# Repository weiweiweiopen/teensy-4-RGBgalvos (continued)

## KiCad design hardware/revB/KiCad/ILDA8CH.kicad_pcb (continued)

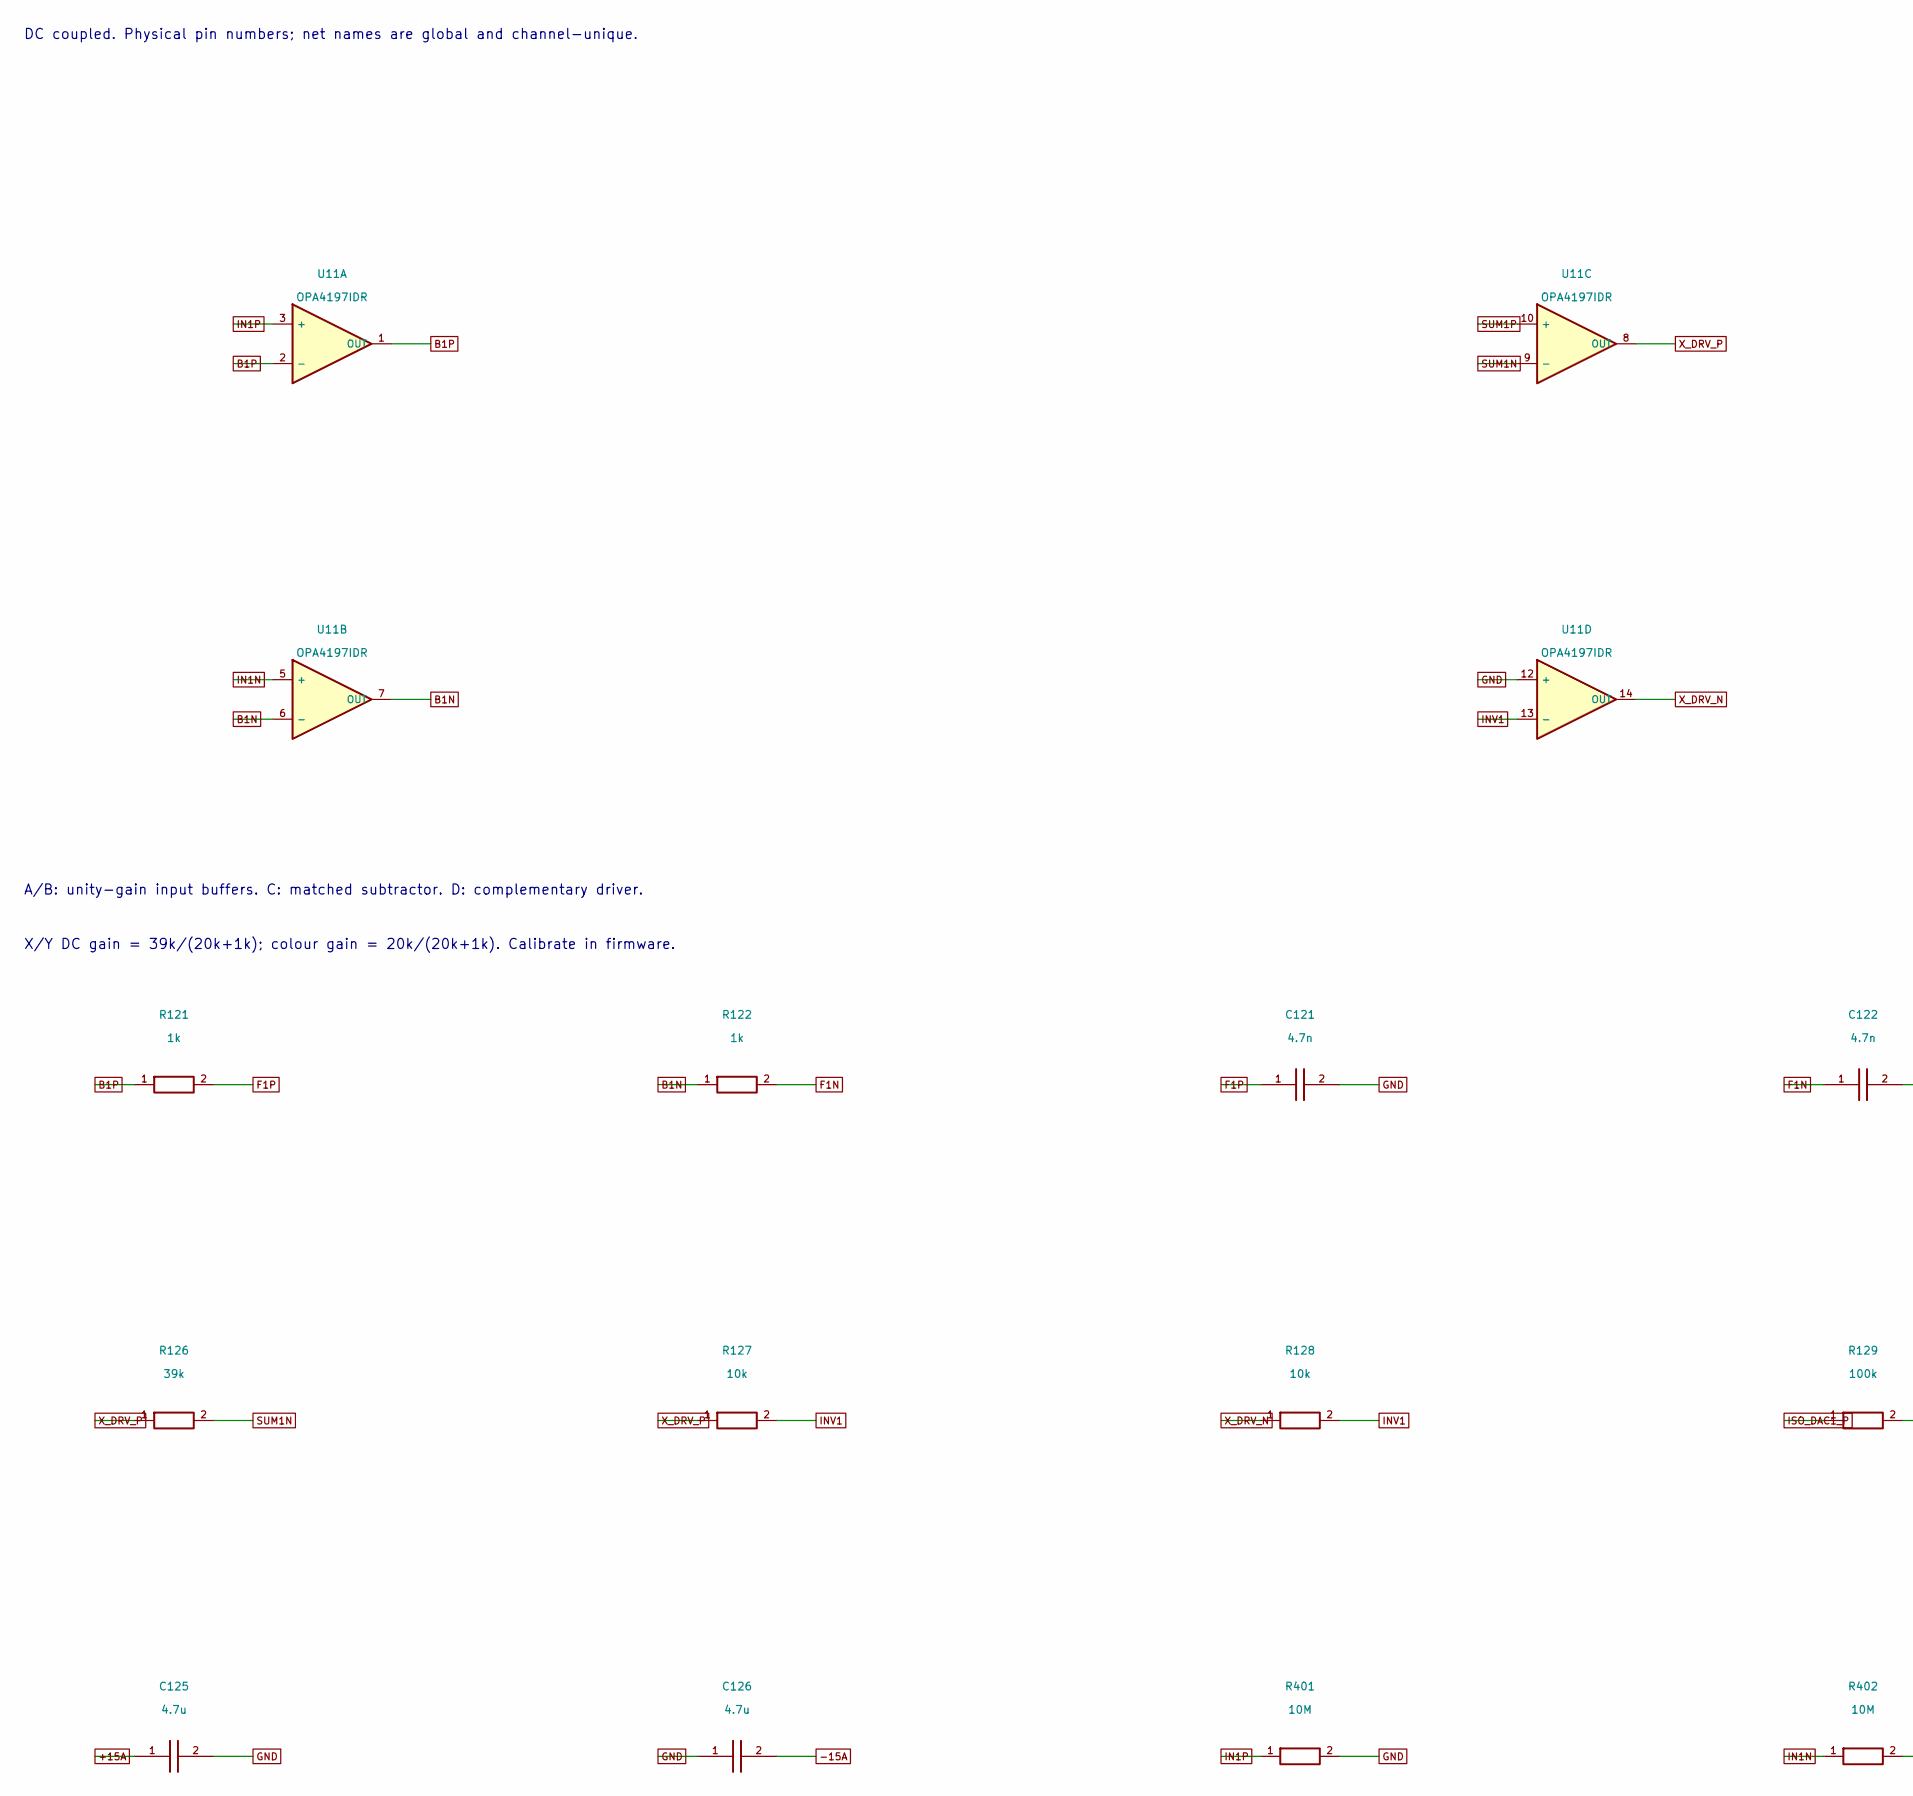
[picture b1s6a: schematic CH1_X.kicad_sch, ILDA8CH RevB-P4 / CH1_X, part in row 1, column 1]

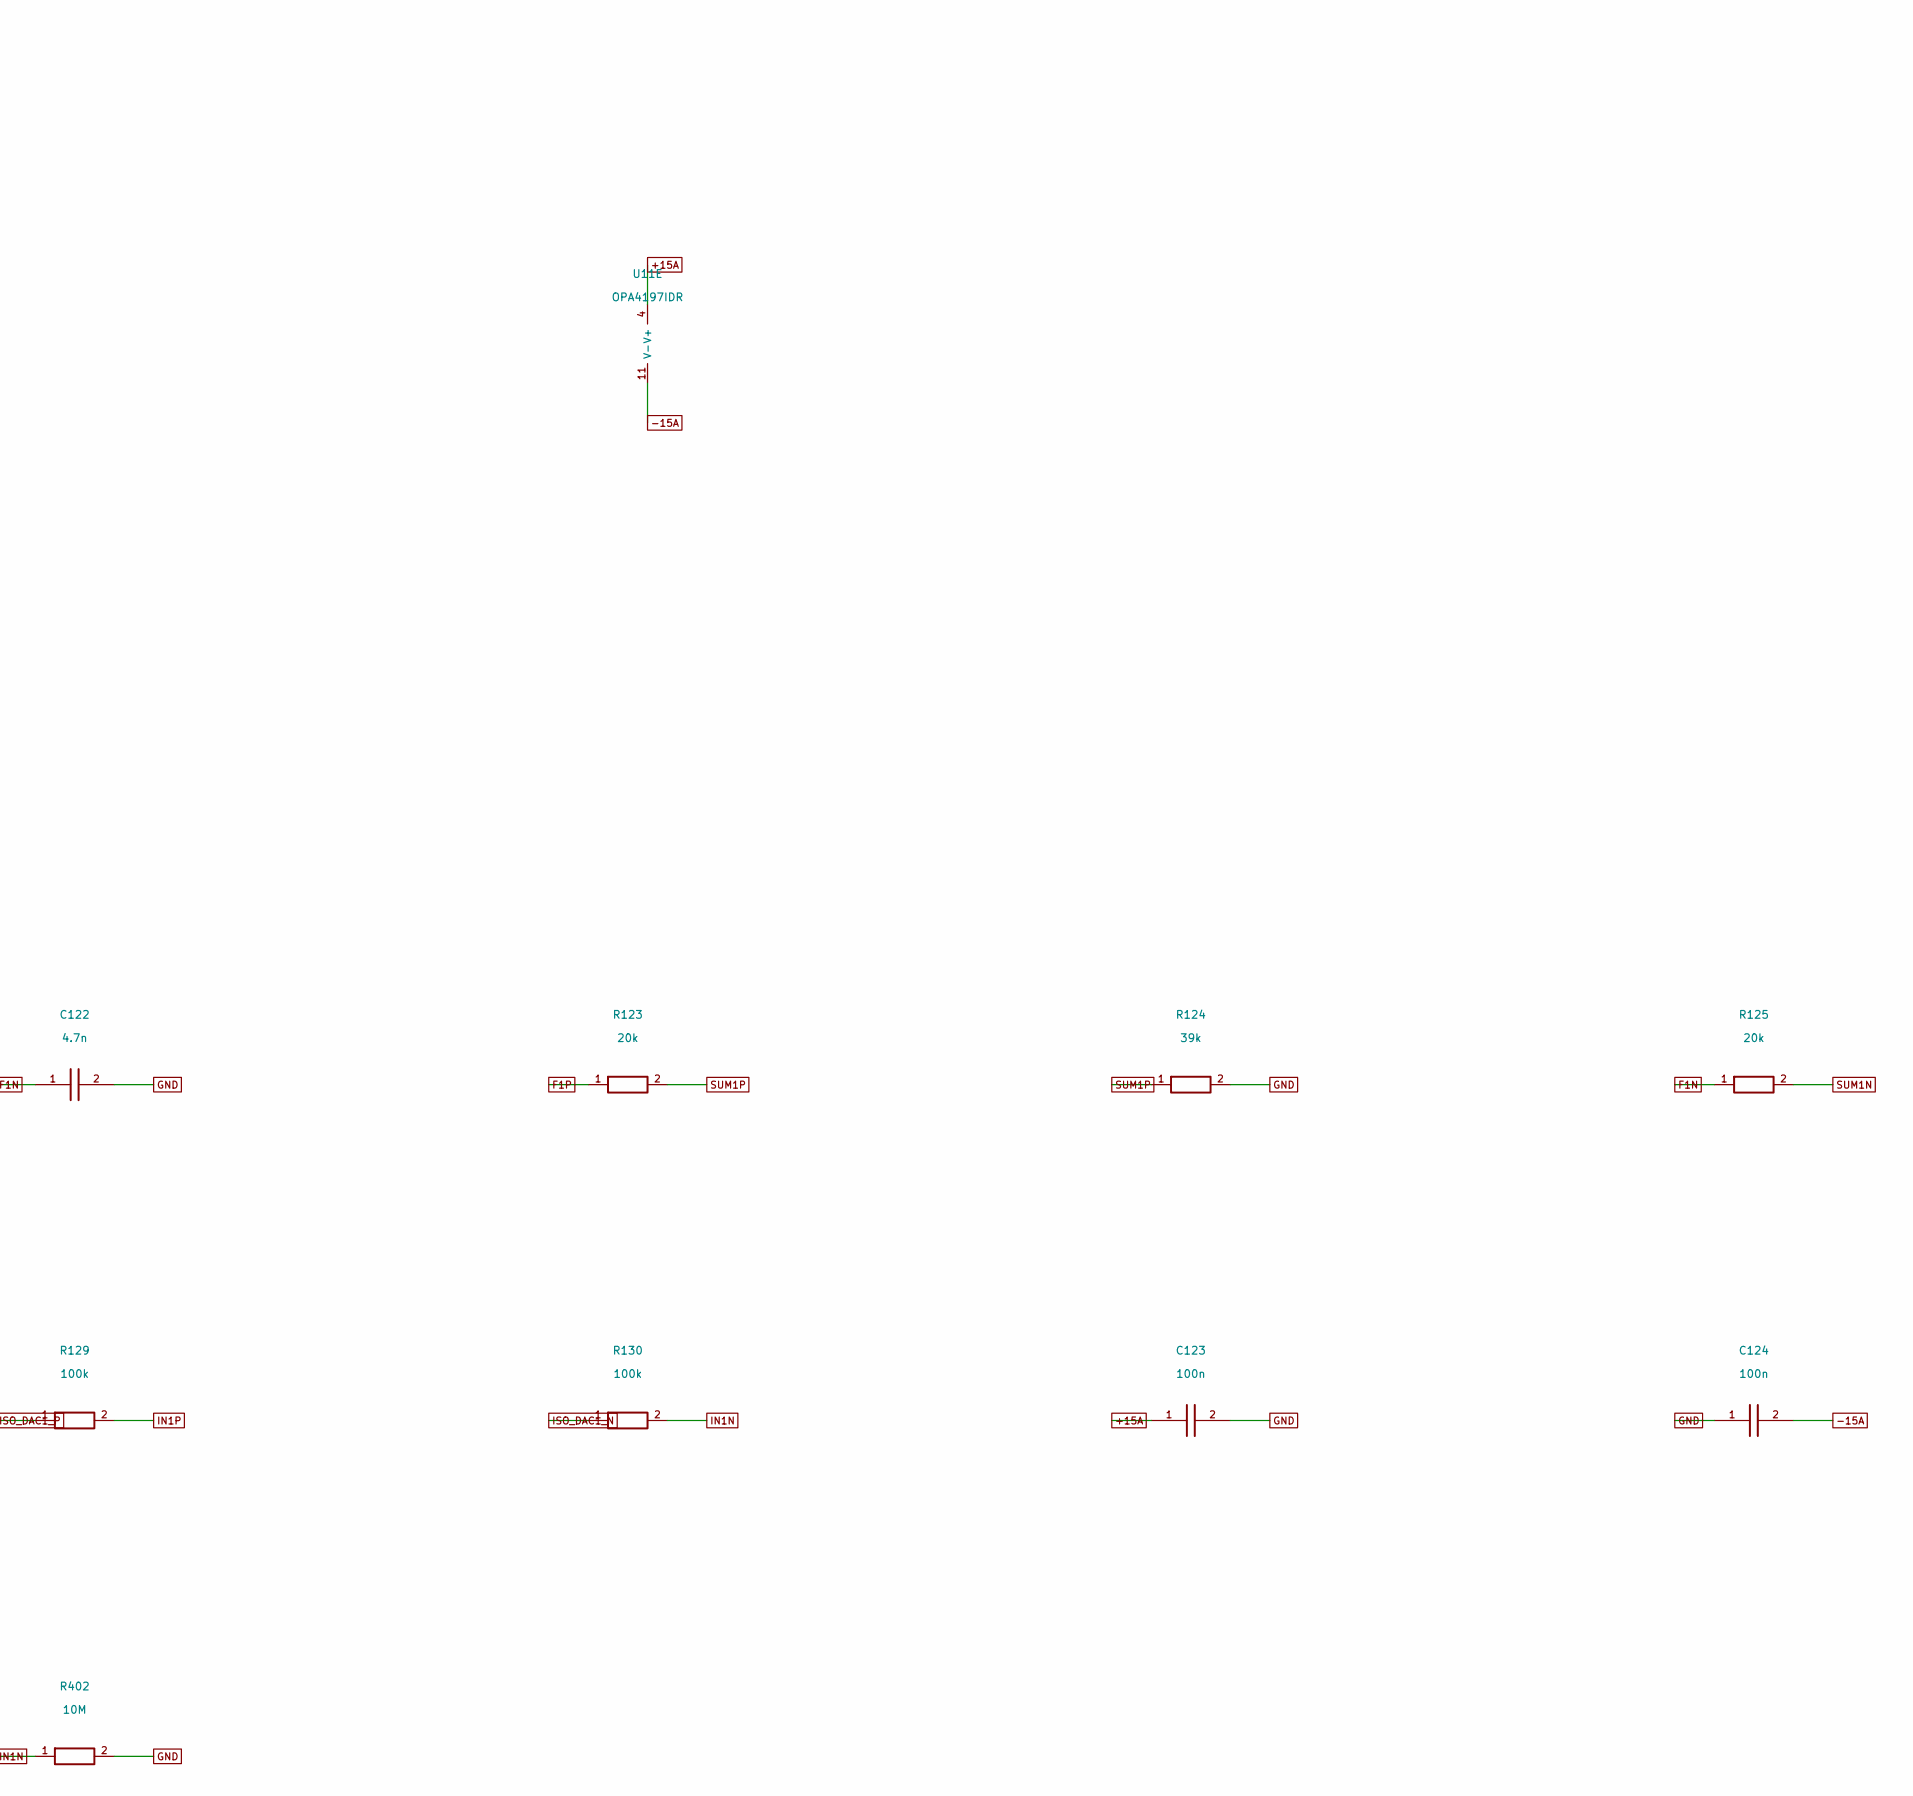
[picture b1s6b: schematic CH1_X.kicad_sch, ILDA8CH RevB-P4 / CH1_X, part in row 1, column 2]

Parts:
C121, C122: 4.7n; Capacitor_SMD__C_0603_1608Metric; MPN GRM1885C1H472JA01D; LCSC C85980
C123, C124: 100n; Capacitor_SMD__C_0603_1608Metric; MPN GRM188R71H104KA93D; LCSC C77055
C125, C126: 4.7u; Capacitor_SMD__C_0805_2012Metric; MPN GRM21BR61E475KA12L; LCSC C77077
R121, R122: 1k; Resistor_SMD__R_0603_1608Metric; MPN RT0603BRD071KL; LCSC C110776
R123, R125: 20k; Resistor_SMD__R_0603_1608Metric; MPN RT0603BRD0720KL; LCSC C723637
R124, R126: 39k; Resistor_SMD__R_0603_1608Metric; MPN RT0603BRD0739KL; LCSC C309652
R127, R128: 10k; Resistor_SMD__R_0603_1608Metric; MPN RT0603BRD0710KL; LCSC C95204
R129, R130: 100k; Resistor_SMD__R_0603_1608Metric; MPN RC0603FR-07100KL; LCSC C14675
R401, R402: 10M; Resistor_SMD__R_0603_1608Metric; MPN RC0603FR-0710ML; LCSC C114606
U11: OPA4197IDR; Package_SO__SOIC-14_3.9x8.7mm_P1.27mm; MPN OPA4197IDR; LCSC C2058532

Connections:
+15A: C123.1, C125.1, U11.4 (V+); also elsewhere on the board
-15A: C124.2, C126.2, U11.11 (V-); also elsewhere on the board
B1N: R122.1, U11.6 (-), U11.7 (OUT)
B1P: R121.1, U11.1 (OUT), U11.2 (-)
F1N: C122.1, R122.2, R125.1
F1P: C121.1, R121.2, R123.1
GND: C121.2, C122.2, C123.2, C124.1, C125.2, C126.1, R124.2, R401.2, R402.2, U11.12 (+); also elsewhere on the board
IN1N: R130.2, R402.1, U11.5 (+)
IN1P: R129.2, R401.1, U11.3 (+)
INV1: R127.2, R128.2, U11.13 (-)
ISO_DAC1_N: R130.1; also elsewhere on the board
ISO_DAC1_P: R129.1; also elsewhere on the board
SUM1N: R125.2, R126.2, U11.9 (-)
SUM1P: R123.2, R124.1, U11.10 (+)
X_DRV_N: R128.1, U11.14 (OUT); also elsewhere on the board
X_DRV_P: R126.1, R127.1, U11.8 (OUT); also elsewhere on the board

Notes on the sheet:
DC coupled. Physical pin numbers; net names are global and channel-unique.
X/Y DC gain = 39k/(20k+1k); colour gain = 20k/(20k+1k). Calibrate in firmware.
A/B: unity-gain input buffers. C: matched subtractor. D: complementary driver.

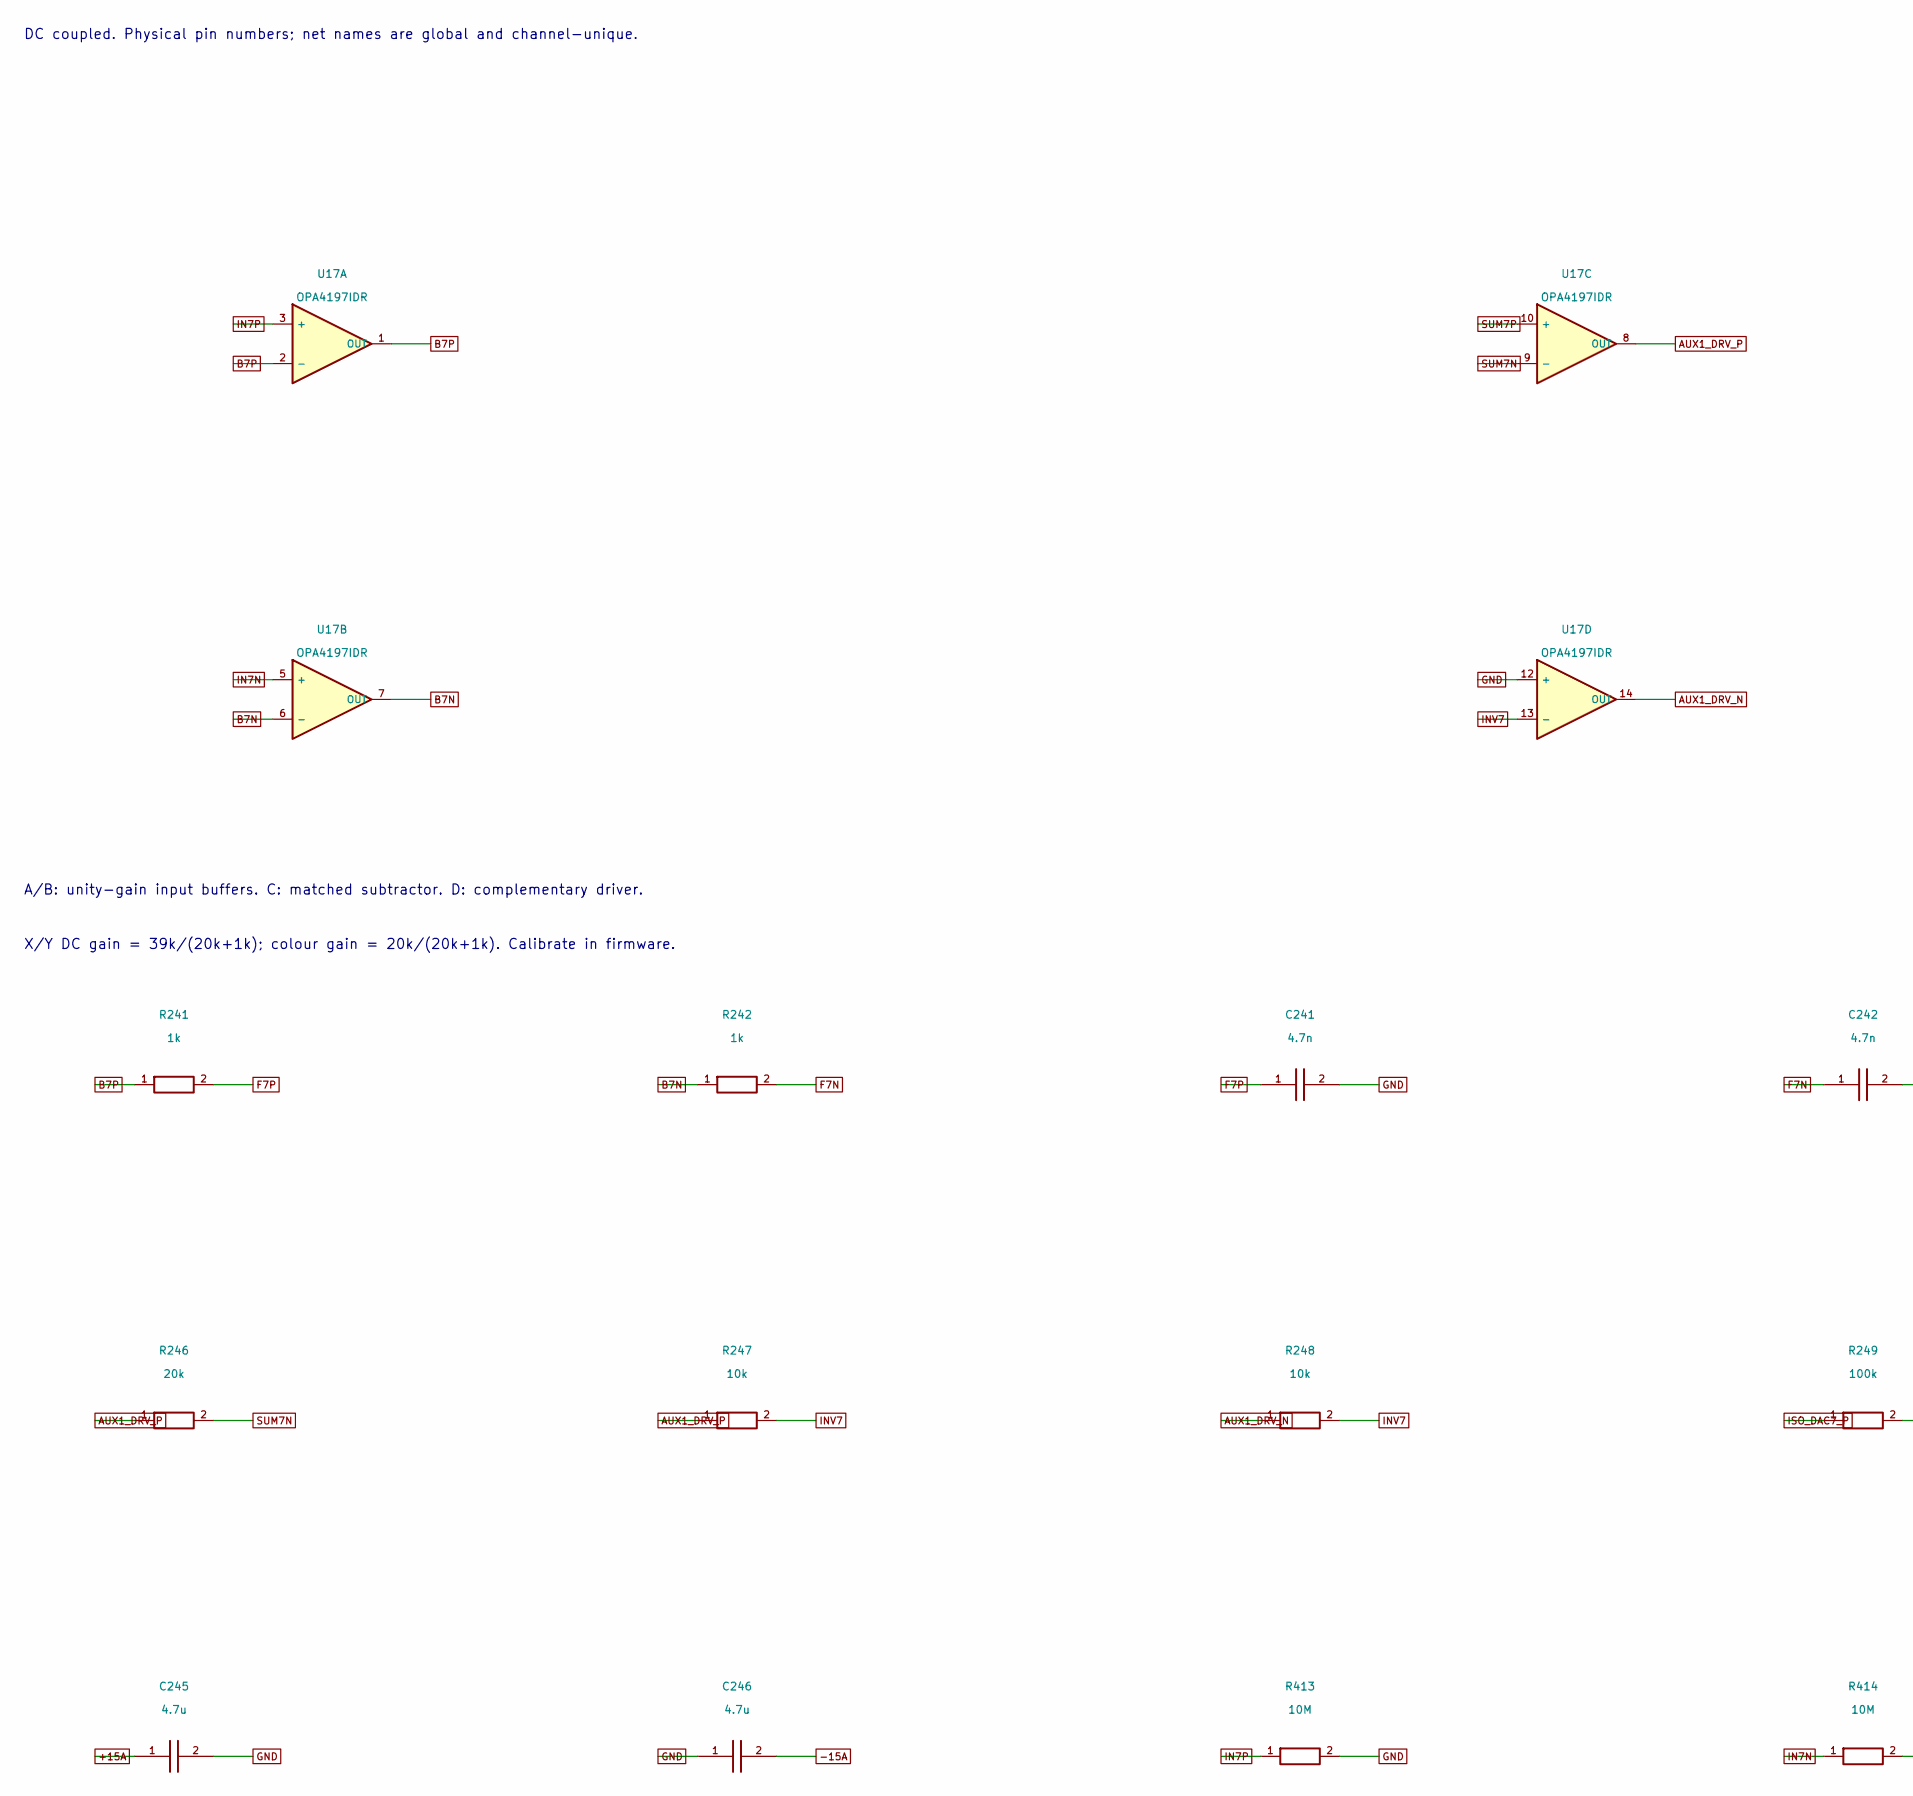
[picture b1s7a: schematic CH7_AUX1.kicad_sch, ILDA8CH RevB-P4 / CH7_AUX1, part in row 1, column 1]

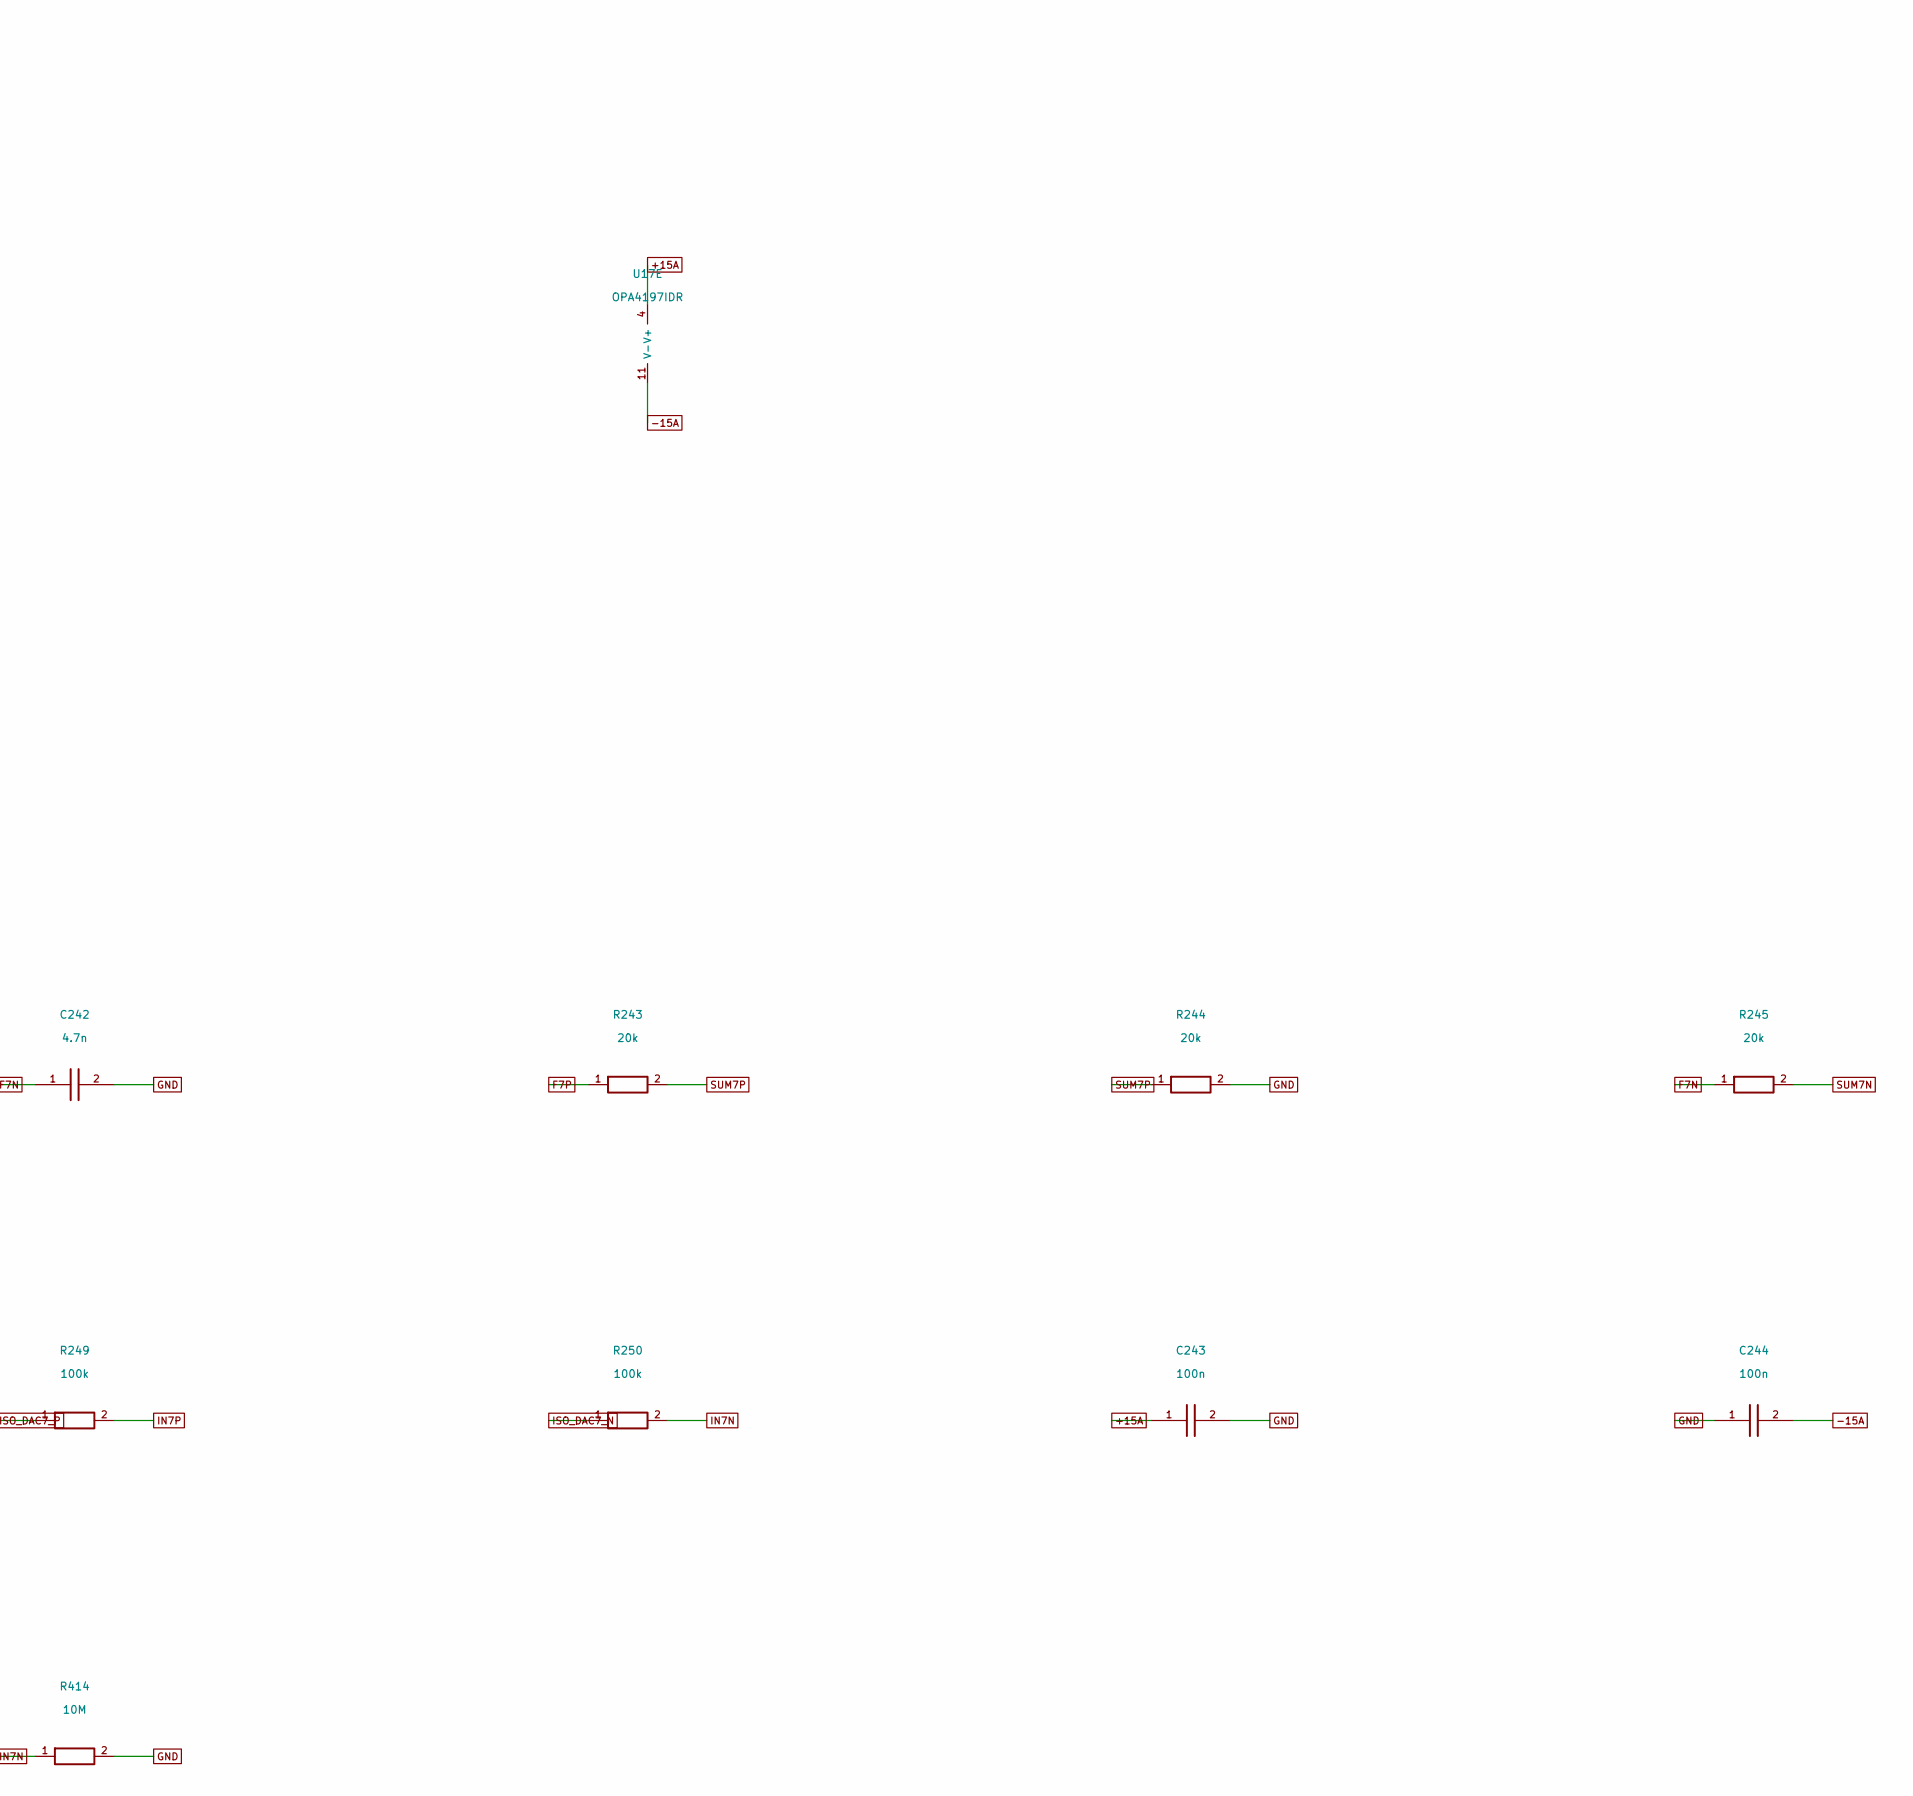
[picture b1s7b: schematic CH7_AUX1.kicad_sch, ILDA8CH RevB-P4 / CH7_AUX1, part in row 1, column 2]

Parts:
C241, C242: 4.7n; Capacitor_SMD__C_0603_1608Metric; MPN GRM1885C1H472JA01D; LCSC C85980
C243, C244: 100n; Capacitor_SMD__C_0603_1608Metric; MPN GRM188R71H104KA93D; LCSC C77055
C245, C246: 4.7u; Capacitor_SMD__C_0805_2012Metric; MPN GRM21BR61E475KA12L; LCSC C77077
R241, R242: 1k; Resistor_SMD__R_0603_1608Metric; MPN RT0603BRD071KL; LCSC C110776
R243, R244, R245, R246: 20k; Resistor_SMD__R_0603_1608Metric; MPN RT0603BRD0720KL; LCSC C723637
R247, R248: 10k; Resistor_SMD__R_0603_1608Metric; MPN RT0603BRD0710KL; LCSC C95204
R249, R250: 100k; Resistor_SMD__R_0603_1608Metric; MPN RC0603FR-07100KL; LCSC C14675
R413, R414: 10M; Resistor_SMD__R_0603_1608Metric; MPN RC0603FR-0710ML; LCSC C114606
U17: OPA4197IDR; Package_SO__SOIC-14_3.9x8.7mm_P1.27mm; MPN OPA4197IDR; LCSC C2058532

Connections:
+15A: C243.1, C245.1, U17.4 (V+); also elsewhere on the board
-15A: C244.2, C246.2, U17.11 (V-); also elsewhere on the board
AUX1_DRV_N: R248.1, U17.14 (OUT); also elsewhere on the board
AUX1_DRV_P: R246.1, R247.1, U17.8 (OUT); also elsewhere on the board
B7N: R242.1, U17.6 (-), U17.7 (OUT)
B7P: R241.1, U17.1 (OUT), U17.2 (-)
F7N: C242.1, R242.2, R245.1
F7P: C241.1, R241.2, R243.1
GND: C241.2, C242.2, C243.2, C244.1, C245.2, C246.1, R244.2, R413.2, R414.2, U17.12 (+); also elsewhere on the board
IN7N: R250.2, R414.1, U17.5 (+)
IN7P: R249.2, R413.1, U17.3 (+)
INV7: R247.2, R248.2, U17.13 (-)
ISO_DAC7_N: R250.1; also elsewhere on the board
ISO_DAC7_P: R249.1; also elsewhere on the board
SUM7N: R245.2, R246.2, U17.9 (-)
SUM7P: R243.2, R244.1, U17.10 (+)

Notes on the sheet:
DC coupled. Physical pin numbers; net names are global and channel-unique.
X/Y DC gain = 39k/(20k+1k); colour gain = 20k/(20k+1k). Calibrate in firmware.
A/B: unity-gain input buffers. C: matched subtractor. D: complementary driver.
